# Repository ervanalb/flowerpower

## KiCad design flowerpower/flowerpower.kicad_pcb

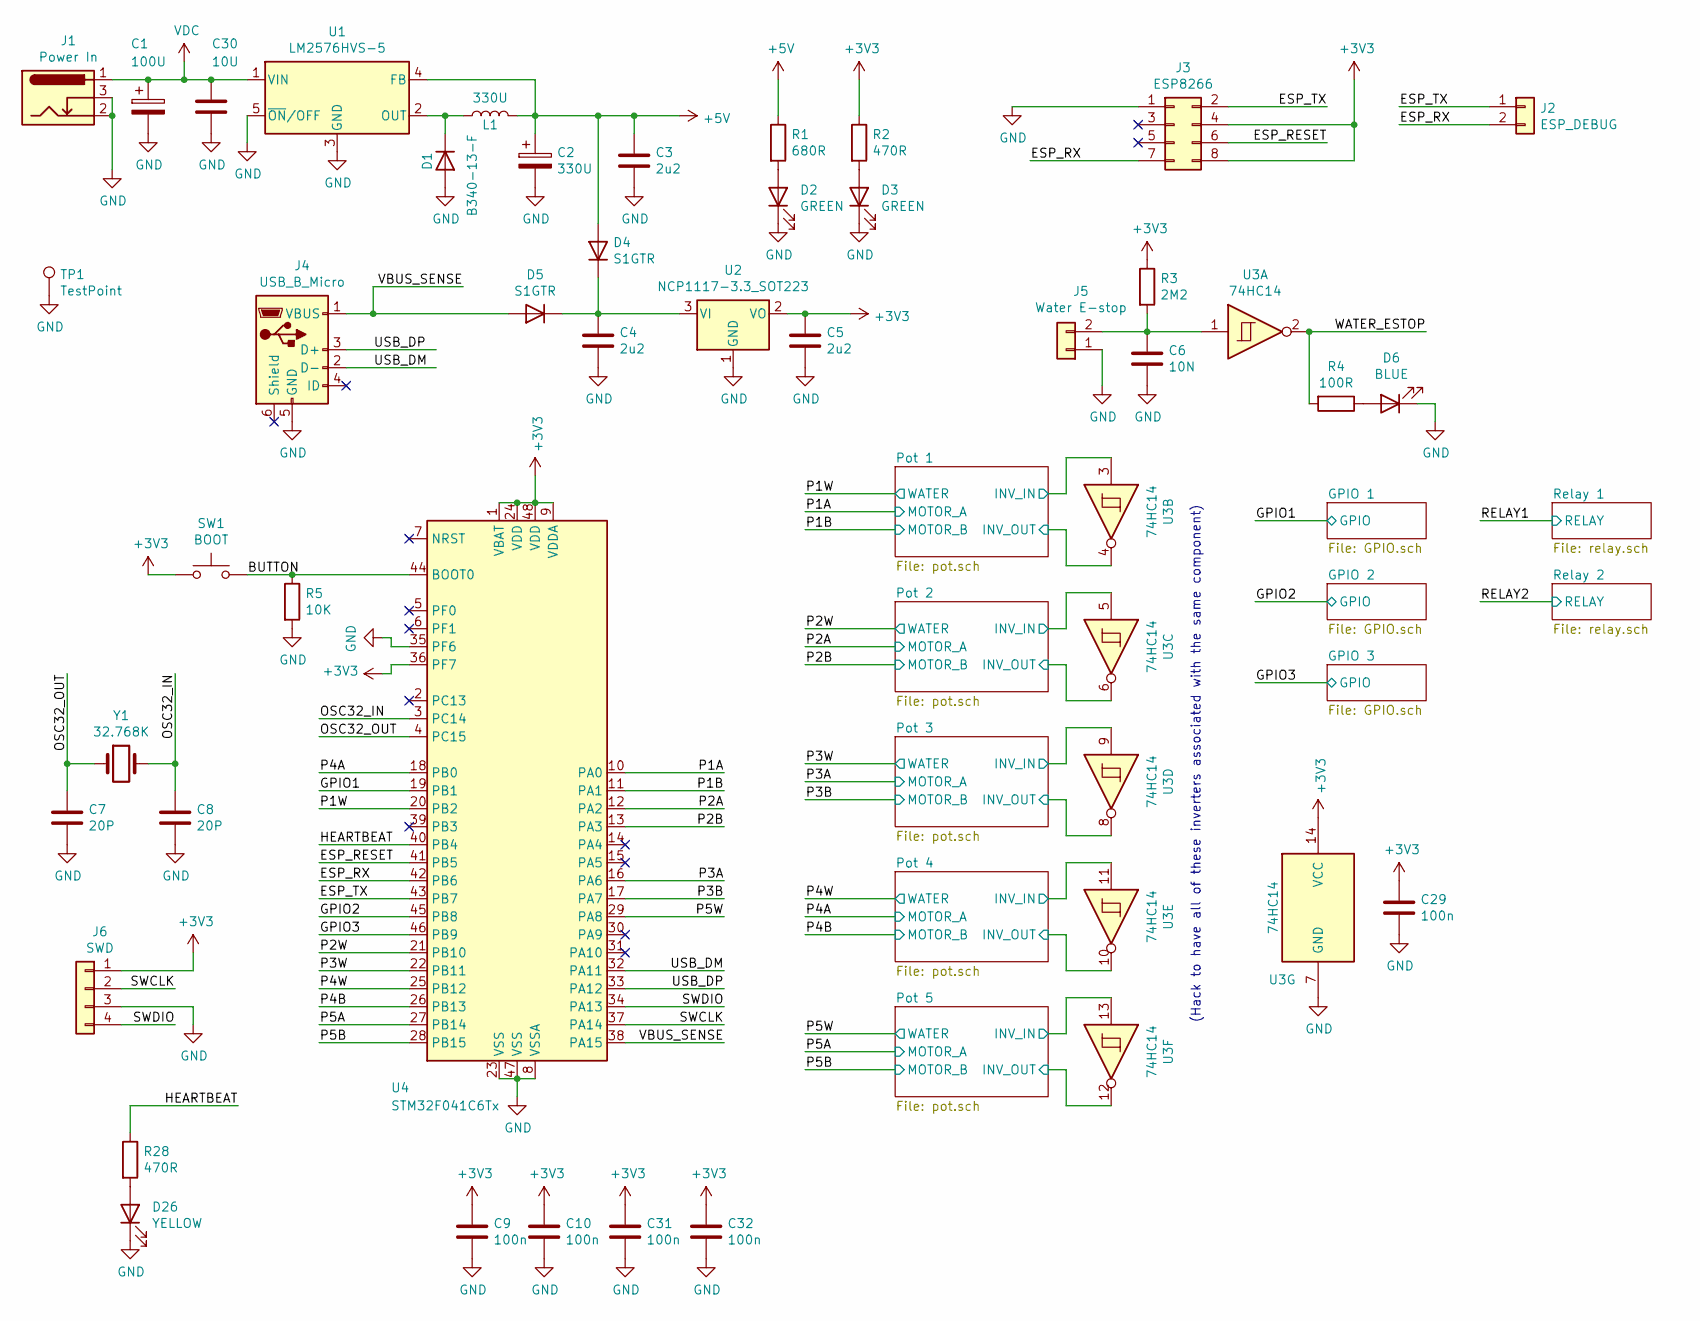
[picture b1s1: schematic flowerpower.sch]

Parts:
C1: 100U; c_elec_10x10
C2: 330U; c_elec_10x10
C3, C4, C5: 2u2; C_0805
C6: 10N; C_0603
C7, C8: 20P; C_0603
C9, C10, C29, C31, C32: 100n; C_0603
C30: 10U; C_1206
D1: B340-13-F; SMC_Standard
D2, D3: GREEN; LED_0603
D4, D5: S1GTR; SMA_Standard
D6: BLUE; LED_0603
D26: YELLOW; LED_0603
J1: Power In; BARREL_JACK
J2: ESP_DEBUG; Pin_Header_Straight_1x02
J3: ESP8266; Pin_Header_Straight_2x04
J4: USB_B_Micro; USB_Micro-B
J5: Water E-stop; Pin_Header_Straight_1x02
J6: SWD; Pin_Header_Straight_1x04
L1: 330U; toroid_14.2_32.5dia
R1: 680R; R_0603
R2, R28: 470R; R_0603
R3: 2M2; R_0603
R4: 100R; R_0603
R5: 10K; R_0603
SW1: BOOT; SW_SPST_TL3342
TP1: TestPoint; Pin_Header_Straight_1x01
U1: LM2576HVS-5; TO-263-5Lead
U2: NCP1117-3.3_SOT223; SOT-223
U3: 74HC14; SOIC-14_3.9x8.7mm_Pitch1.27mm
U4: STM32F041C6Tx; LQFP-48_7x7mm_Pitch0.5mm
Y1: 32.768K; SOJ-4

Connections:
+3V3: C5.1, C9.1, C10.1, C29.1, C31.1, C32.1, J3.4, J3.8, J6.1, R2.1, R3.1, SW1.1, U2.2 (VO), U3.14 (VCC), U4.1 (VBAT), U4.9 (VDDA), U4.24 (VDD), U4.36 (PF7), U4.48 (VDD); also elsewhere on the board
+5V: C2.1, C3.1, D4.2 (A), L1.2, R1.1, U1.4 (FB); also elsewhere on the board
/BUTTON: R5.1, SW1.2, U4.44 (BOOT0)
/ESP_RESET: J3.6, U4.41 (PB5)
/ESP_RX: J2.2, J3.7, U4.42 (PB6)
/ESP_TX: J2.1, J3.2, U4.43 (PB7)
/GPIO1: U4.19 (PB1); also elsewhere on the board
/GPIO2: U4.45 (PB8); also elsewhere on the board
/GPIO3: U4.46 (PB9); also elsewhere on the board
/HEARTBEAT: R28.1, U4.40 (PB4)
/OSC32_IN: C8.1, U4.3 (PC14), Y1.2
/OSC32_OUT: C7.1, U4.4 (PC15), Y1.1
/P1A: U4.10 (PA0); also elsewhere on the board
/P1B: U4.11 (PA1); also elsewhere on the board
/P1W: U3.4, U4.20 (PB2); also elsewhere on the board
/P2A: U4.12 (PA2); also elsewhere on the board
/P2B: U4.13 (PA3); also elsewhere on the board
/P2W: U3.6, U4.21 (PB10); also elsewhere on the board
/P3A: U4.16 (PA6); also elsewhere on the board
/P3B: U4.17 (PA7); also elsewhere on the board
/P3W: U3.8, U4.22 (PB11); also elsewhere on the board
/P4A: U4.18 (PB0); also elsewhere on the board
/P4B: U4.26 (PB13); also elsewhere on the board
/P4W: U3.10, U4.25 (PB12); also elsewhere on the board
/P5A: U4.27 (PB14); also elsewhere on the board
/P5B: U4.28 (PB15); also elsewhere on the board
/P5W: U3.12, U4.29 (PA8); also elsewhere on the board
/Pot 1/INV_IN: U3.3; also elsewhere on the board
/Pot 2/INV_IN: U3.5; also elsewhere on the board
/Pot 3/INV_IN: U3.9; also elsewhere on the board
/Pot 4/INV_IN: U3.11; also elsewhere on the board
/Pot 5/INV_IN: U3.13; also elsewhere on the board
/SWCLK: J6.2, U4.37 (PA14)
/SWDIO: J6.4, U4.34 (PA13)
/USB_DM: J4.2 (D-), U4.32 (PA11)
/USB_DP: J4.3 (D+), U4.33 (PA12)
/VBUS_SENSE: D5.2 (A), J4.1 (VBUS), U4.38 (PA15)
/WATER_ESTOP: R4.2, U3.2
GND: C1.2, C2.2, C3.2, C4.2, C5.2, C6.2, C7.2, C8.2, C9.2, C10.2, C29.2, C30.2, C31.2, C32.2, D1.2 (A), D2.1 (K), D3.1 (K), D6.1 (K), D26.1 (K), J1.2, J1.3, J3.1, J4.5 (GND), J5.1, J6.3, R5.2, TP1.1, U1.3 (GND), U1.5 (~ON~/OFF), U2.1 (GND), U3.7 (GND), U4.8 (VSSA), U4.23 (VSS), U4.35 (PF6), U4.47 (VSS); also elsewhere on the board
unnamed: C4.1, D4.1 (K), D5.1 (K), U2.3 (VI)
unnamed: C6.1, J5.2, R3.2, U3.1
unnamed: D1.1 (K), L1.1, U1.2 (OUT)
unnamed: D2.2 (A), R1.2
unnamed: D3.2 (A), R2.2
unnamed: D6.2 (A), R4.1
unnamed: D26.2 (A), R28.2
VDC: C1.1, C30.1, J1.1, U1.1 (VIN); also elsewhere on the board

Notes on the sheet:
(Hack to have all of these inverters associated with the same component)

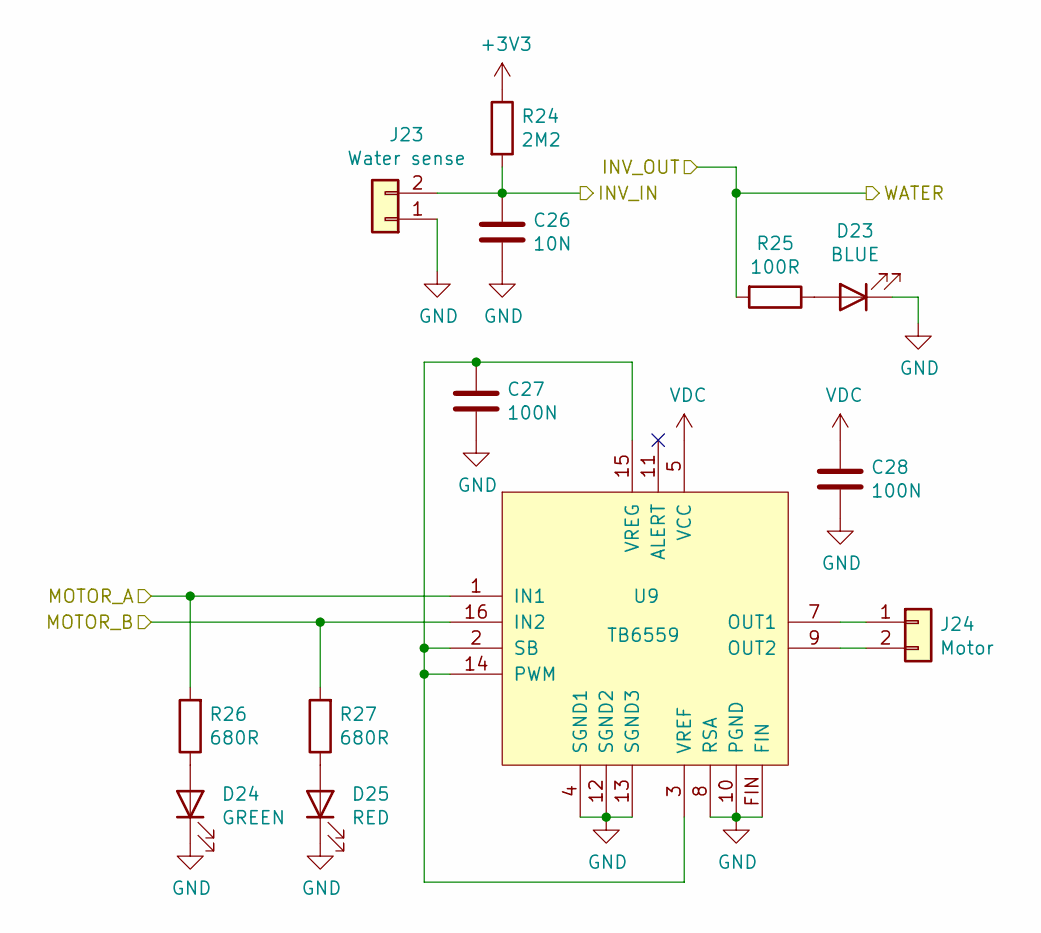
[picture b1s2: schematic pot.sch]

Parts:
C11: 10N; C_0603
C12, C13: 100N; C_0603
D7: BLUE; LED_0603
D8: GREEN; LED_0603
D9: RED; LED_0603
J7: Water sense; Pin_Header_Straight_1x02
J8: Motor; Pin_Header_Straight_1x02
R6: 2M2; R_0603
R7: 100R; R_0603
R8, R9: 680R; R_0603
U5: TB6559; 16-hsop-fins

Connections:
+3V3: R6.1; also elsewhere on the board
/P1A: R8.2, U5.1 (IN1); also elsewhere on the board
/P1B: R9.2, U5.16 (IN2); also elsewhere on the board
/P1W: R7.2; also elsewhere on the board
/Pot 1/INV_IN: C11.1, J7.2, R6.2; also elsewhere on the board
GND: C11.2, C12.2, C13.2, D7.1 (K), D8.1 (K), D9.1 (K), J7.1, U5.4 (SGND1), U5.8 (RSA), U5.10 (PGND), U5.12 (SGND2), U5.13 (SGND3), U5.FIN; also elsewhere on the board
unnamed: C12.1, U5.2 (SB), U5.3 (VREF), U5.14 (PWM), U5.15 (VREG)
unnamed: D7.2 (A), R7.1
unnamed: D8.2 (A), R8.1
unnamed: D9.2 (A), R9.1
unnamed: J8.1, U5.7 (OUT1)
unnamed: J8.2, U5.9 (OUT2)
VDC: C13.1, U5.5 (VCC); also elsewhere on the board

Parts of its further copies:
C17, C20, C23, C26: 10N; C_0603
C18, C19, C21, C22, C24, C25, C27, C28: 100N; C_0603
D14, D17, D20, D23: BLUE; LED_0603
D15, D18, D21, D24: GREEN; LED_0603
D16, D19, D22, D25: RED; LED_0603
J17, J19, J21, J23: Water sense; Pin_Header_Straight_1x02
J18, J20, J22, J24: Motor; Pin_Header_Straight_1x02
R12, R16, R20, R24: 2M2; R_0603
R13, R17, R21, R25: 100R; R_0603
R14, R15, R18, R19, R22, R23, R26, R27: 680R; R_0603
U6, U7, U8, U9: TB6559; 16-hsop-fins

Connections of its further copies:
+3V3: R12.1, R16.1, R20.1, R24.1; also elsewhere on the board
/P2A: R14.2, U6.1 (IN1); also elsewhere on the board
/P2B: R15.2, U6.16 (IN2); also elsewhere on the board
/P2W: R13.2; also elsewhere on the board
/P3A: R18.2, U7.1 (IN1); also elsewhere on the board
/P3B: R19.2, U7.16 (IN2); also elsewhere on the board
/P3W: R17.2; also elsewhere on the board
/P4A: R22.2, U8.1 (IN1); also elsewhere on the board
/P4B: R23.2, U8.16 (IN2); also elsewhere on the board
/P4W: R21.2; also elsewhere on the board
/P5A: R26.2, U9.1 (IN1); also elsewhere on the board
/P5B: R27.2, U9.16 (IN2); also elsewhere on the board
/P5W: R25.2; also elsewhere on the board
/Pot 2/INV_IN: C17.1, J17.2, R12.2; also elsewhere on the board
/Pot 3/INV_IN: C20.1, J19.2, R16.2; also elsewhere on the board
/Pot 4/INV_IN: C23.1, J21.2, R20.2; also elsewhere on the board
/Pot 5/INV_IN: C26.1, J23.2, R24.2; also elsewhere on the board
GND: C17.2, C18.2, C19.2, C20.2, C21.2, C22.2, C23.2, C24.2, C25.2, C26.2, C27.2, C28.2, D14.1 (K), D15.1 (K), D16.1 (K), D17.1 (K), D18.1 (K), D19.1 (K), D20.1 (K), D21.1 (K), D22.1 (K), D23.1 (K), D24.1 (K), D25.1 (K), J17.1, J19.1, J21.1, J23.1, U6.4 (SGND1), U6.8 (RSA), U6.10 (PGND), U6.12 (SGND2), U6.13 (SGND3), U6.FIN, U7.4 (SGND1), U7.8 (RSA), U7.10 (PGND), U7.12 (SGND2), U7.13 (SGND3), U7.FIN, U8.4 (SGND1), U8.8 (RSA), U8.10 (PGND), U8.12 (SGND2), U8.13 (SGND3), U8.FIN, U9.4 (SGND1), U9.8 (RSA), U9.10 (PGND), U9.12 (SGND2), U9.13 (SGND3), U9.FIN; also elsewhere on the board
unnamed: C18.1, U6.2 (SB), U6.3 (VREF), U6.14 (PWM), U6.15 (VREG)
unnamed: C21.1, U7.2 (SB), U7.3 (VREF), U7.14 (PWM), U7.15 (VREG)
unnamed: C24.1, U8.2 (SB), U8.3 (VREF), U8.14 (PWM), U8.15 (VREG)
unnamed: C27.1, U9.2 (SB), U9.3 (VREF), U9.14 (PWM), U9.15 (VREG)
unnamed: D14.2 (A), R13.1
unnamed: D15.2 (A), R14.1
unnamed: D16.2 (A), R15.1
unnamed: D17.2 (A), R17.1
unnamed: D18.2 (A), R18.1
unnamed: D19.2 (A), R19.1
unnamed: D20.2 (A), R21.1
unnamed: D21.2 (A), R22.1
unnamed: D22.2 (A), R23.1
unnamed: D23.2 (A), R25.1
unnamed: D24.2 (A), R26.1
unnamed: D25.2 (A), R27.1
unnamed: J18.1, U6.7 (OUT1)
unnamed: J18.2, U6.9 (OUT2)
unnamed: J20.1, U7.7 (OUT1)
unnamed: J20.2, U7.9 (OUT2)
unnamed: J22.1, U8.7 (OUT1)
unnamed: J22.2, U8.9 (OUT2)
unnamed: J24.1, U9.7 (OUT1)
unnamed: J24.2, U9.9 (OUT2)
VDC: C19.1, C22.1, C25.1, C28.1, U6.5 (VCC), U7.5 (VCC), U8.5 (VCC), U9.5 (VCC); also elsewhere on the board

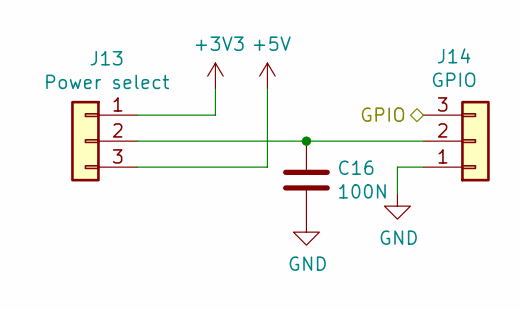
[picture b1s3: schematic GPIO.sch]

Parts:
C14: 100N; C_0603
J9: Power select; Pin_Header_Straight_1x03
J10: GPIO; Pin_Header_Straight_1x03

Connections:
+3V3: J9.1; also elsewhere on the board
+5V: J9.3; also elsewhere on the board
/GPIO1: J10.3; also elsewhere on the board
GND: C14.2, J10.1; also elsewhere on the board
unnamed: C14.1, J9.2, J10.2

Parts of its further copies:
C15, C16: 100N; C_0603
J11, J13: Power select; Pin_Header_Straight_1x03
J12, J14: GPIO; Pin_Header_Straight_1x03

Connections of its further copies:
+3V3: J11.1, J13.1; also elsewhere on the board
+5V: J11.3, J13.3; also elsewhere on the board
/GPIO2: J12.3; also elsewhere on the board
/GPIO3: J14.3; also elsewhere on the board
GND: C15.2, C16.2, J12.1, J14.1; also elsewhere on the board
unnamed: C15.1, J11.2, J12.2
unnamed: C16.1, J13.2, J14.2

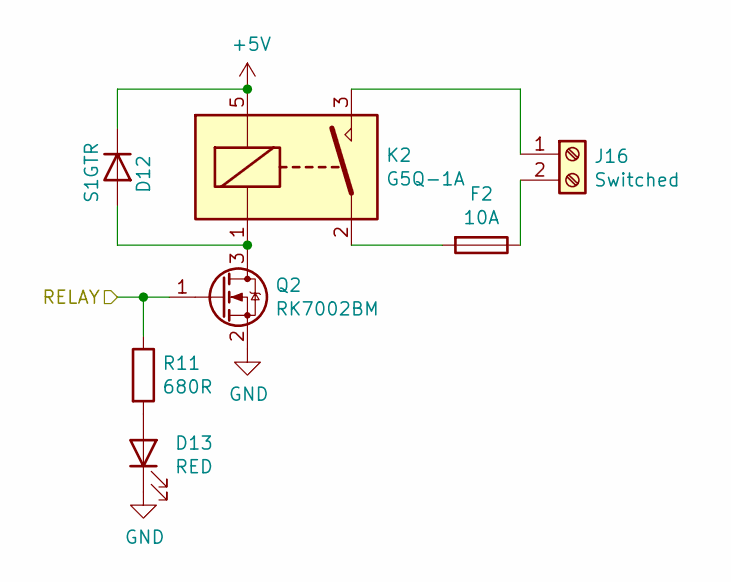
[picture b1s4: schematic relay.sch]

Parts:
D10: S1GTR; SMA_Standard
D11: RED; LED_0603
F1: 10A; Fuseholder5x20_horiz_SemiClosed_Casing10x25mm
J15: Switched; TerminalBlock_Pheonix_PT-3.5mm_2pol
K1: G5Q-1A; Relay_SPST_Omron-G5Q-1A
Q1: RK7002BM; SOT-23
R10: 680R; R_0603

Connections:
+5V: D10.1 (K), K1.5; also elsewhere on the board
/RELAY1: Q1.1 (G), R10.1
GND: D11.1 (K), Q1.2 (S); also elsewhere on the board
unnamed: D10.2 (A), K1.1, Q1.3 (D)
unnamed: D11.2 (A), R10.2
unnamed: F1.1, J15.2
unnamed: F1.2, K1.2
unnamed: J15.1, K1.3

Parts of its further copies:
D12: S1GTR; SMA_Standard
D13: RED; LED_0603
F2: 10A; Fuseholder5x20_horiz_SemiClosed_Casing10x25mm
J16: Switched; TerminalBlock_Pheonix_PT-3.5mm_2pol
K2: G5Q-1A; Relay_SPST_Omron-G5Q-1A
Q2: RK7002BM; SOT-23
R11: 680R; R_0603

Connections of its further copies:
+5V: D12.1 (K), K2.5; also elsewhere on the board
/RELAY2: Q2.1 (G), R11.1
GND: D13.1 (K), Q2.2 (S); also elsewhere on the board
unnamed: D12.2 (A), K2.1, Q2.3 (D)
unnamed: D13.2 (A), R11.2
unnamed: F2.1, J16.2
unnamed: F2.2, K2.2
unnamed: J16.1, K2.3

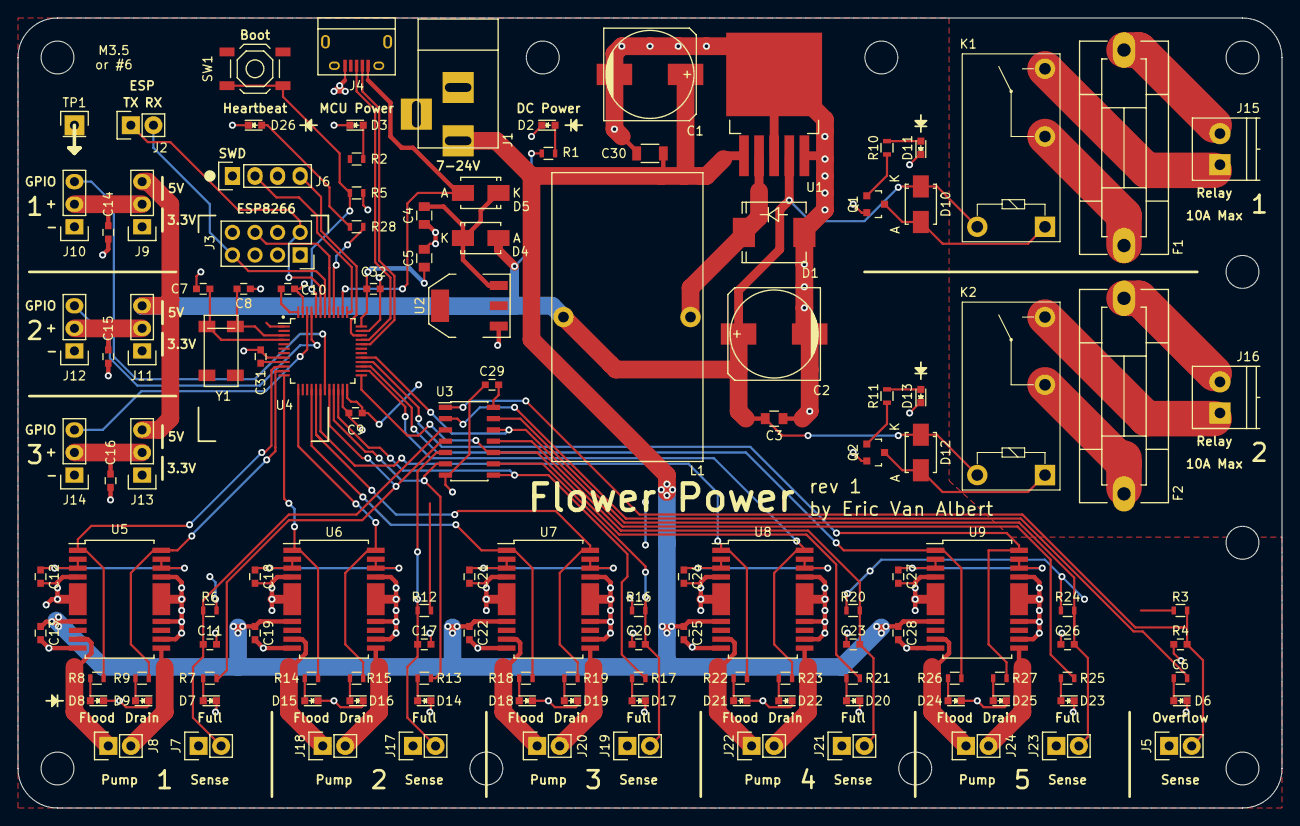
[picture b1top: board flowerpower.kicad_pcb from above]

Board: 2 copper layers, 142.2 x 88.9 mm, 129 parts (0 on the bottom side), 92 nets.

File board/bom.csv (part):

"Source:","/home/eric/flowerpower/flowerpower/flowerpower.sch"
"Date:","Tue 06 Oct 2020 09:06:13 PM EDT"
"Tool:","Eeschema 5.1.6"
"Generator:","/usr/share/kicad/plugins/bom_csv_grouped_by_value.py"
"Component Count:","128"

"Individual Components:"

"Item","Qty","Reference(s)","Value","LibPart","Footprint","Datasheet"
"","","C1","100U","Device:CP","Capacitors_SMD:c_elec_10x10","~"
"","","C2","330U","Device:CP","Capacitors_SMD:c_elec_10x10","~"
"","","C3","2u2","Device:C","Capacitors_SMD:C_0805","~"
"","","C4","2u2","Device:C","Capacitors_SMD:C_0805","~"
"","","C5","2u2","Device:C","Capacitors_SMD:C_0805","~"
"","","C6","10N","Device:C","Capacitors_SMD:C_0603","~"
"","","C7","20P","Device:C","Capacitors_SMD:C_0603","~"
"","","C8","20P","Device:C","Capacitors_SMD:C_0603","~"
"","","C9","100n","Device:C","Capacitors_SMD:C_0603","~"
"","","C10","100n","Device:C","Capacitors_SMD:C_0603","~"
"","","C11","10N","Device:C","Capacitors_SMD:C_0603","~"
"","","C12","100N","Device:C","Capacitors_SMD:C_0603","~"
"","","C13","100N","Device:C","Capacitors_SMD:C_0603","~"
"","","C14","100N","Device:C","Capacitors_SMD:C_0603","~"
"","","C15","100N","Device:C","Capacitors_SMD:C_0603","~"
"","","C16","100N","Device:C","Capacitors_SMD:C_0603","~"
"","","C17","10N","Device:C","Capacitors_SMD:C_0603","~"
"","","C18","100N","Device:C","Capacitors_SMD:C_0603","~"
"","","C19","100N","Device:C","Capacitors_SMD:C_0603","~"
"","","C20","10N","Device:C","Capacitors_SMD:C_0603","~"
"","","C21","100N","Device:C","Capacitors_SMD:C_0603","~"
"","","C22","100N","Device:C","Capacitors_SMD:C_0603","~"
"","","C23","10N","Device:C","Capacitors_SMD:C_0603","~"
"","","C24","100N","Device:C","Capacitors_SMD:C_0603","~"
"","","C25","100N","Device:C","Capacitors_SMD:C_0603","~"
"","","C26","10N","Device:C","Capacitors_SMD:C_0603","~"
"","","C27","100N","Device:C","Capacitors_SMD:C_0603","~"
"","","C28","100N","Device:C","Capacitors_SMD:C_0603","~"
"","","C29","100n","Device:C","Capacitors_SMD:C_0603","~"
"","","C30","10U","Device:C","Capacitors_SMD:C_1206","~"
"","","C31","100n","Device:C","Capacitors_SMD:C_0603","~"
"","","C32","100n","Device:C","Capacitors_SMD:C_0603","~"
"","","D1","B340-13-F","Device:D","Diodes_SMD:SMC_Standard","~"
"","","D2","GREEN","Device:LED","LEDs:LED_0603","~"
"","","D3","GREEN","Device:LED","LEDs:LED_0603","~"
"","","D4","S1GTR","Device:D","Diodes_SMD:SMA_Standard","~"
"","","D5","S1GTR","Device:D","Diodes_SMD:SMA_Standard","~"
"","","D6","BLUE","Device:LED","LEDs:LED_0603","~"
"","","D7","BLUE","Device:LED","LEDs:LED_0603","~"
"","","D8","GREEN","Device:LED","LEDs:LED_0603","~"
"","","D9","RED","Device:LED","LEDs:LED_0603","~"
"","","D10","S1GTR","Device:D","Diodes_SMD:SMA_Standard","~"
"","","D11","RED","Device:LED","LEDs:LED_0603","~"
"","","D12","S1GTR","Device:D","Diodes_SMD:SMA_Standard","~"
"","","D13","RED","Device:LED","LEDs:LED_0603","~"
"","","D14","BLUE","Device:LED","LEDs:LED_0603","~"
"","","D15","GREEN","Device:LED","LEDs:LED_0603","~"
"","","D16","RED","Device:LED","LEDs:LED_0603","~"
"","","D17","BLUE","Device:LED","LEDs:LED_0603","~"
"","","D18","GREEN","Device:LED","LEDs:LED_0603","~"
"","","D19","RED","Device:LED","LEDs:LED_0603","~"
"","","D20","BLUE","Device:LED","LEDs:LED_0603","~"
"","","D21","GREEN","Device:LED","LEDs:LED_0603","~"
"","","D22","RED","Device:LED","LEDs:LED_0603","~"
"","","D23","BLUE","Device:LED","LEDs:LED_0603","~"
"","","D24","GREEN","Device:LED","LEDs:LED_0603","~"
"","","D25","RED","Device:LED","LEDs:LED_0603","~"
"","","D26","YELLOW","Device:LED","LEDs:LED_0603","~"
"","","F1","10A","Device:Fuse","Fuse_Holders_and_Fuses:Fuseholder5x20_horiz_SemiClosed_Casing10x25mm","~"
"","","F2","10A","Device:Fuse","Fuse_Holders_and_Fuses:Fuseholder5x20_horiz_SemiClosed_Casing10x25mm","~"
"","","J1","Power In","Connector:Barrel_Jack_Switch","Connect:BARREL_JACK","~"
"","","J2","ESP_DEBUG","Connector_Generic:Conn_01x02","Pin_Headers:Pin_Header_Straight_1x02","~"
"","","J3","ESP8266","Connector_Generic:Conn_02x04_Odd_Even","Pin_Headers:Pin_Header_Straight_2x04","~"
"","","J4","USB_B_Micro","Connector:USB_B_Micro","Connect:USB_Micro-B","~"
"","","J5","Water E-stop","Connector_Generic:Conn_01x02","Pin_Headers:Pin_Header_Straight_1x02","~"
"","","J6","SWD","Connector_Generic:Conn_01x04","Pin_Headers:Pin_Header_Straight_1x04","~"
"","","J7","Water sense","Connector_Generic:Conn_01x02","Pin_Headers:Pin_Header_Straight_1x02","~"
"","","J8","Motor","Connector_Generic:Conn_01x02","Pin_Headers:Pin_Header_Straight_1x02","~"
"","","J9","Power select","Connector_Generic:Conn_01x03","Pin_Headers:Pin_Header_Straight_1x03","~"
"","","J10","GPIO","Connector_Generic:Conn_01x03","Pin_Headers:Pin_Header_Straight_1x03","~"
"","","J11","Power select","Connector_Generic:Conn_01x03","Pin_Headers:Pin_Header_Straight_1x03","~"
"","","J12","GPIO","Connector_Generic:Conn_01x03","Pin_Headers:Pin_Header_Straight_1x03","~"
"","","J13","Power select","Connector_Generic:Conn_01x03","Pin_Headers:Pin_Header_Straight_1x03","~"
"","","J14","GPIO","Connector_Generic:Conn_01x03","Pin_Headers:Pin_Header_Straight_1x03","~"
"","","J15","Switched","Connector:Screw_Terminal_01x02","Terminal_Blocks:TerminalBlock_Pheonix_PT-3.5mm_2pol","~"
"","","J16","Switched","Connector:Screw_Terminal_01x02","Terminal_Blocks:TerminalBlock_Pheonix_PT-3.5mm_2pol","~"
"","","J17","Water sense","Connector_Generic:Conn_01x02","Pin_Headers:Pin_Header_Straight_1x02","~"
"","","J18","Motor","Connector_Generic:Conn_01x02","Pin_Headers:Pin_Header_Straight_1x02","~"
"","","J19","Water sense","Connector_Generic:Conn_01x02","Pin_Headers:Pin_Header_Straight_1x02","~"
"","","J20","Motor","Connector_Generic:Conn_01x02","Pin_Headers:Pin_Header_Straight_1x02","~"
"","","J21","Water sense","Connector_Generic:Conn_01x02","Pin_Headers:Pin_Header_Straight_1x02","~"
"","","J22","Motor","Connector_Generic:Conn_01x02","Pin_Headers:Pin_Header_Straight_1x02","~"
"","","J23","Water sense","Connector_Generic:Conn_01x02","Pin_Headers:Pin_Header_Straight_1x02","~"
"","","J24","Motor","Connector_Generic:Conn_01x02","Pin_Headers:Pin_Header_Straight_1x02","~"
"","","K1","G5Q-1A","Relay:G5Q-1A","Relay_THT:Relay_SPST_Omron-G5Q-1A","https://www.omron.com/ecb/products/pdf/en-g5q.pdf"
"","","K2","G5Q-1A","Relay:G5Q-1A","Relay_THT:Relay_SPST_Omron-G5Q-1A","https://www.omron.com/ecb/products/pdf/en-g5q.pdf"
"","","L1","330U","Device:L","flowerpower:toroid_14.2_32.5dia","~"
"","","Q1","RK7002BM","Transistor_FET:2N7002","TO_SOT_Packages_SMD:SOT-23","https://www.fairchildsemi.com/datasheets/2N/2N7002.pdf"
"","","Q2","RK7002BM","Transistor_FET:2N7002","TO_SOT_Packages_SMD:SOT-23","https://www.fairchildsemi.com/datasheets/2N/2N7002.pdf"
"","","R1","680R","Device:R","Resistors_SMD:R_0603","~"
"","","R2","470R","Device:R","Resistors_SMD:R_0603","~"
"","","R3","2M2","Device:R","Resistors_SMD:R_0603","~"
"","","R4","100R","Device:R","Resistors_SMD:R_0603","~"
"","","R5","10K","Device:R","Resistors_SMD:R_0603","~"
"","","R6","2M2","Device:R","Resistors_SMD:R_0603","~"
"","","R7","100R","Device:R","Resistors_SMD:R_0603","~"
"","","R8","680R","Device:R","Resistors_SMD:R_0603","~"
"","","R9","680R","Device:R","Resistors_SMD:R_0603","~"
"","","R10","680R","Device:R","Resistors_SMD:R_0603","~"
"","","R11","680R","Device:R","Resistors_SMD:R_0603","~"
"","","R12","2M2","Device:R","Resistors_SMD:R_0603","~"
"","","R13","100R","Device:R","Resistors_SMD:R_0603","~"
"","","R14","680R","Device:R","Resistors_SMD:R_0603","~"
"","","R15","680R","Device:R","Resistors_SMD:R_0603","~"
"","","R16","2M2","Device:R","Resistors_SMD:R_0603","~"
"","","R17","100R","Device:R","Resistors_SMD:R_0603","~"
"","","R18","680R","Device:R","Resistors_SMD:R_0603","~"
"","","R19","680R","Device:R","Resistors_SMD:R_0603","~"
"","","R20","2M2","Device:R","Resistors_SMD:R_0603","~"
"","","R21","100R","Device:R","Resistors_SMD:R_0603","~"
"","","R22","680R","Device:R","Resistors_SMD:R_0603","~"
"","","R23","680R","Device:R","Resistors_SMD:R_0603","~"
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
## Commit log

2020-09-15 Add basic water level controller
2020-09-15 Add MQTT to plant.py
2020-09-15 Working on RPI
2020-09-30 Schematic and some footprint association
2020-10-04 beginning layout
2020-10-04 tweaking layout
2020-10-05 finish layout
2020-10-05 silkscreen
2020-10-06 Final tweaks
2020-10-06 generate rev1 gerbers
2020-10-09 zipped up gerbs
2020-10-09 Add no-op firmware
2020-10-10 FreeRTOS tweaks to get things working
2020-10-10 start adding USB support
2020-10-10 Untested USB receive function
2020-10-16 Noodling around with the firmware some more (USB RX seems to be working)
2020-10-16 USB sending and receiving
2020-10-16 Add in comms abstraction layer
2020-10-16 Comms seem to be working after adding USB disconnect logic
2020-10-18 Further refinement with regards to RTC, comms, heartbeat, watchdog
2020-10-18 Freeze linker script
2020-10-18 Start to flesh out architecture for state and communication
2020-10-18 Massage some RAM sizes
2020-10-19 Reading commands working
2020-10-19 Basic relay setting
2020-10-19 Rearrange flash writing slightly
2020-10-19 Convert to macros, but something funny is going on
2020-10-20 Flash write working (when not debugging) along with relay schedules
2020-10-20 Add pots & global config
2020-10-20 Start adding more pot variables
2020-10-22 First pass at implementing pot control loop
2020-10-22 Fix some bugs in the pot filling and draining logic
2020-10-24 Add scheduling of feeding times
2020-10-25 change pot defaults
